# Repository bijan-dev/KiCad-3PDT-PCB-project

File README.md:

# KiCad-3PDT-PCB-project
A 3PDT PCB for guitar pedals

Hello, this is a KiCad project for a 3PDT PCB board.
This will allow a guitar pedal with a 3PDT [like this](https://stompboxparts.com/footswitches/3pdt-footswitch-solder-lug-vimex/) to be wired in true bypass.

* JI = Input Jack
* IN = PCB Input
* LED = LED connection (assumes an offboard current limiting resistor eg. 4.7k Ohm. Please add one if your effect PCB doesn't have one)
* GND = Ground connection
* OUT = PCB Output
* JO = Output Jack

The wire pads have a pitch of 2.54mm (0.1") to match that of common ribbon cables.

Board width is 17.5mm, height is 20.5mm.

Huge thank you to [Mad Bean](https://www.madbeanpedals.com/) for the pad and 3PDT footprints, their footprint library is the GOAT.

---

**This board is now verified!** I ordered some copies from OshPark, and used one in a new build. It works! It's suprisingly tiny!

---

# If you would like to order one

The gerber files are included in the repo.

Click into the `3pdt_pcb_fab_files.zip` file in this repo, then download that zip file.

Then you can use a board fabricator like JLCPCB and upload that zip onto their site.

If you need the gerber files compressed in a different format than .zip, I've included them in the folder `3pdt_pcb_fab_files`.

Here's where to put the file on JLCPCBs website:

Once you drag the .zip onto there, it'll load this page with the PCB, and lots of options for it.
You can click "PCB Qty" to change the number of boards to get. I usually leave everything else default,
except for Surface Finish - LeadFree HASL (personal preference).

Other PCB fab sites should work very similarly.

---

# Here's screenshots of the schematic and PCB layout:

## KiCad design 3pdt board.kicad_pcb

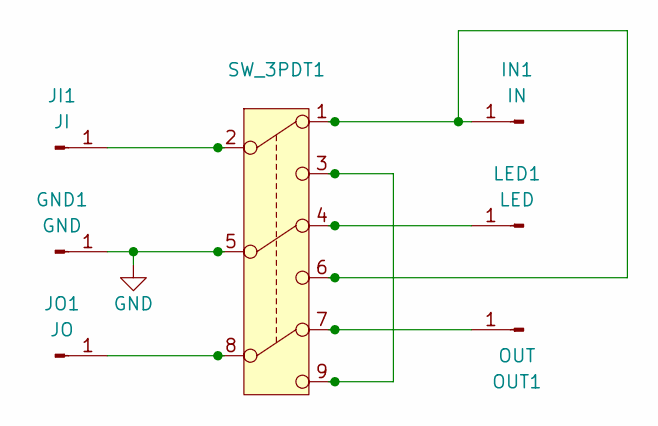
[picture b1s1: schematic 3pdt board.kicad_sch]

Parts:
GND1: GND; PAD1
IN1: IN; PAD1
JI1: JI; PAD1
JO1: JO; PAD1
LED1: LED; PAD1
OUT1: OUT; PAD1
SW_3PDT1: 3PDT.LUGS.KR.NO_CIRCLE

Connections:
GND: GND1.1, SW_3PDT1.5
unnamed: IN1.1, SW_3PDT1.1, SW_3PDT1.6
unnamed: JI1.1, SW_3PDT1.2
unnamed: JO1.1, SW_3PDT1.8
unnamed: LED1.1, SW_3PDT1.4
unnamed: OUT1.1, SW_3PDT1.7
unnamed: SW_3PDT1.3, SW_3PDT1.9

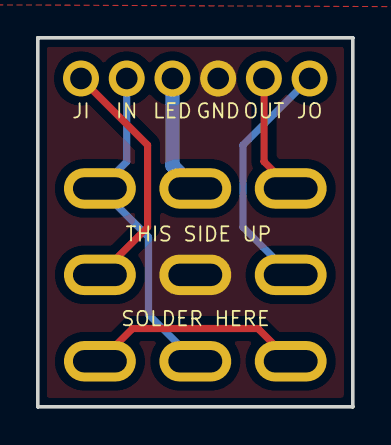
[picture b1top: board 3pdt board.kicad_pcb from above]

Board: 2 copper layers, 17.5 x 20.5 mm, 7 parts (0 on the bottom side), 7 nets.

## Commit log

2025-03-01 Create LICENSE
2025-03-01 Rename LICENSE to LICENSE.json
2025-03-01 Create placeholder
2025-03-01 Rename 3pdt render.png to 3pdt_render.png
2025-03-01 Rename JLCPCB board page.png to JLCPCB_board_page.png
2025-03-01 Rename JLCPCB.png to JLCPCB_website.png
2025-03-01 update directory name
2025-03-01 rearrange files
2025-03-01 update image paths
2025-03-01 new 3pdt image
2025-03-01 add image of where to download
2025-03-01 explain files are gerber
2025-03-01 disclaimer
2025-03-01 add ty to mad bean
2025-03-01 add pad note
2025-03-01 clarify compression
2025-03-01 add schem and pcb layout images
2025-03-01 add panel option
2025-03-01 missing space
2025-03-01 panel pricing
2025-03-01 clarify language
2025-03-01 add line break
2025-03-01 remove panel section
2025-03-01 add line break again
2025-04-22 board is now verified, add images
2025-04-22 image wasn't showing
2025-04-22 wrong image file extension
